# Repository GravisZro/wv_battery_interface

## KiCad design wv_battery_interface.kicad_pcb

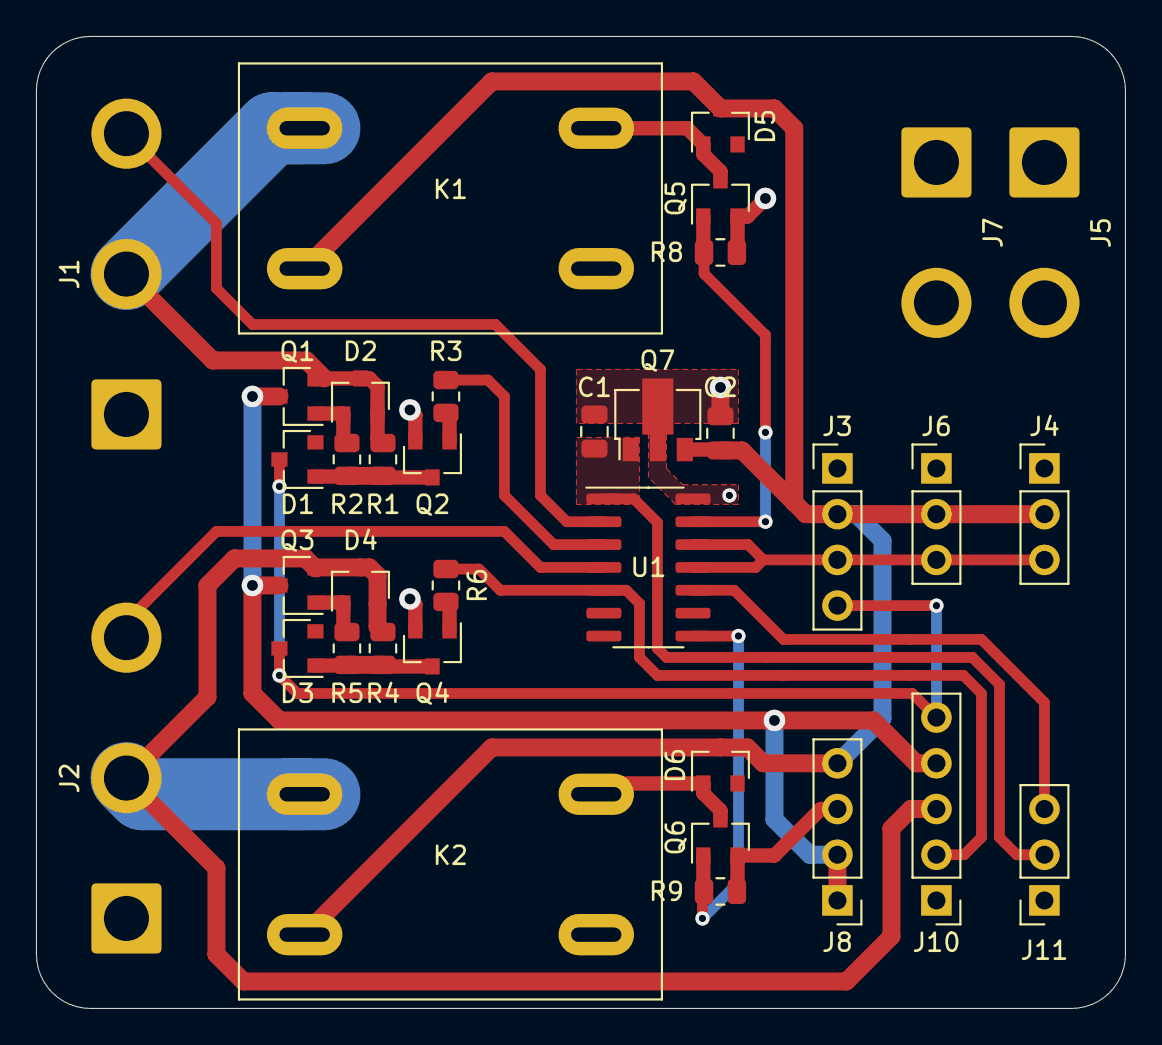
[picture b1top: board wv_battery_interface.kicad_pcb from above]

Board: 2 copper layers, 60.5 x 54.0 mm, 36 parts (0 on the bottom side), 24 nets.

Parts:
C1: 0.33μF, 10V; C_0805_2012Metric
C2: 0.1μF, 25V; C_0805_2012Metric
D1, D3: 100V; D_SOT-23_ANK
D2, D4: BZX84-C10; D_SOT-23_ANK
D5, D6: 25V; D_SOT-23_ANK
J1, J2: Conn_01x03; SolderWire-2sqmm_1x03_P7.8mm_D2mm_OD3.9mm
J3, J8: Conn_01x04; PinHeader_1x04_P2.54mm_Vertical
J4, J6: Conn_01x03; PinHeader_1x03_P2.54mm_Vertical
J5, J7: Conn_01x02; SolderWire-2sqmm_1x02_P7.8mm_D2mm_OD3.9mm
J10: Conn_01x05; PinHeader_1x05_P2.54mm_Vertical
J11: Conn_01x03; PinSocket_1x03_P2.54mm_Vertical
K1, K2: 301-1A-C-R1-U03-12VDC; Relay_1-Form-A_Song_Chuan-301-1A
Q1, Q3: P-channel MOSFET, 100V@1A; SOT-23
Q2, Q4: MMBT5551L; SOT-23
Q5, Q6: NX138; SOT-23
Q7: AS78LXX; SOT-89-3
R1, R3, R4, R6: 100kΩ; R_0805_2012Metric
R2, R5: 1MΩ; R_0805_2012Metric
R8, R9: 10kΩ; R_0805_2012Metric
U1: ATtiny204-SS; SOIC-14_3.9x8.7mm_P1.27mm

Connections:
1wire_bus: J3.3, J4.3, J6.3, U1.11, U1.12
14V: C2.1, D5.1, D6.1, J3.2, J4.2, J6.2, J8.4, K1.85, K2.85, Q7.3
+5V: C1.2, J11.2, Q7.1, U1.1
+BATT1: D2.1, J1.2, K1.30, Q1.2, R1.1
+BATT2: D4.1, J2.2, J10.3, K2.30, Q3.2, R4.1
/Relay 1/Enable: Q5.1, R8.2, U1.13
/Relay 2/Enable: Q6.1, R9.2, U1.8
/Soft Latch Switch 1/Enable: R3.1, U1.3
/Soft Latch Switch 1/Switch-to-GND: D1.1, D3.1, J3.4, J10.5
/Soft Latch Switch 2/Enable: J10.2, R6.1, U1.5
BatteryPower: J8.1, J8.2, J10.4, Q1.3, Q3.3
GND: C1.1, C2.2, J1.1, J2.1, J3.1, J4.1, J5.1, J6.1, J7.1, J8.3, J10.1, J11.1, Q2.2, Q4.2, Q5.2, Q6.2, Q7.2, R8.1, R9.1, U1.14
unnamed: D1.2, Q2.3, R1.2, R2.1
unnamed: D2.2, Q1.1, R2.2
unnamed: D3.2, Q4.3, R4.2, R5.1
unnamed: D4.2, Q3.1, R5.2
unnamed: D5.2, K1.86, Q5.3
unnamed: D6.2, K2.86, Q6.3
unnamed: J1.3, U1.2
unnamed: J2.3, U1.4
unnamed: J11.3, U1.10
unnamed: Q2.1, R3.2
unnamed: Q4.1, R6.2
RelayPower: J5.2, J7.2, K1.87, K2.87

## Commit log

2021-10-04 debug version
2021-10-05 alternate component values added
2021-10-05 add rounded edges
2021-10-05 schematic update
2021-10-05 schematic cleanup
